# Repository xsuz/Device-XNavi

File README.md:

# Device-Template

> A template for building applications for Twelite

This project is developed and maintained by the xsuz

## Dependencies

To build embedded programs using this template you'll need:

- KiCad Version: 8.0.0, or a newer version.

- Git client

- Github CLI (optional)

## Using this template with GitHub CLI

```sh
gh repo create ${repo name} --private --template https://github.com/xsuz/Device-Template -c
cd ${repo name}
sh ./setup.sh
```

注. 自分のアカウントにRepositoryが作られます。

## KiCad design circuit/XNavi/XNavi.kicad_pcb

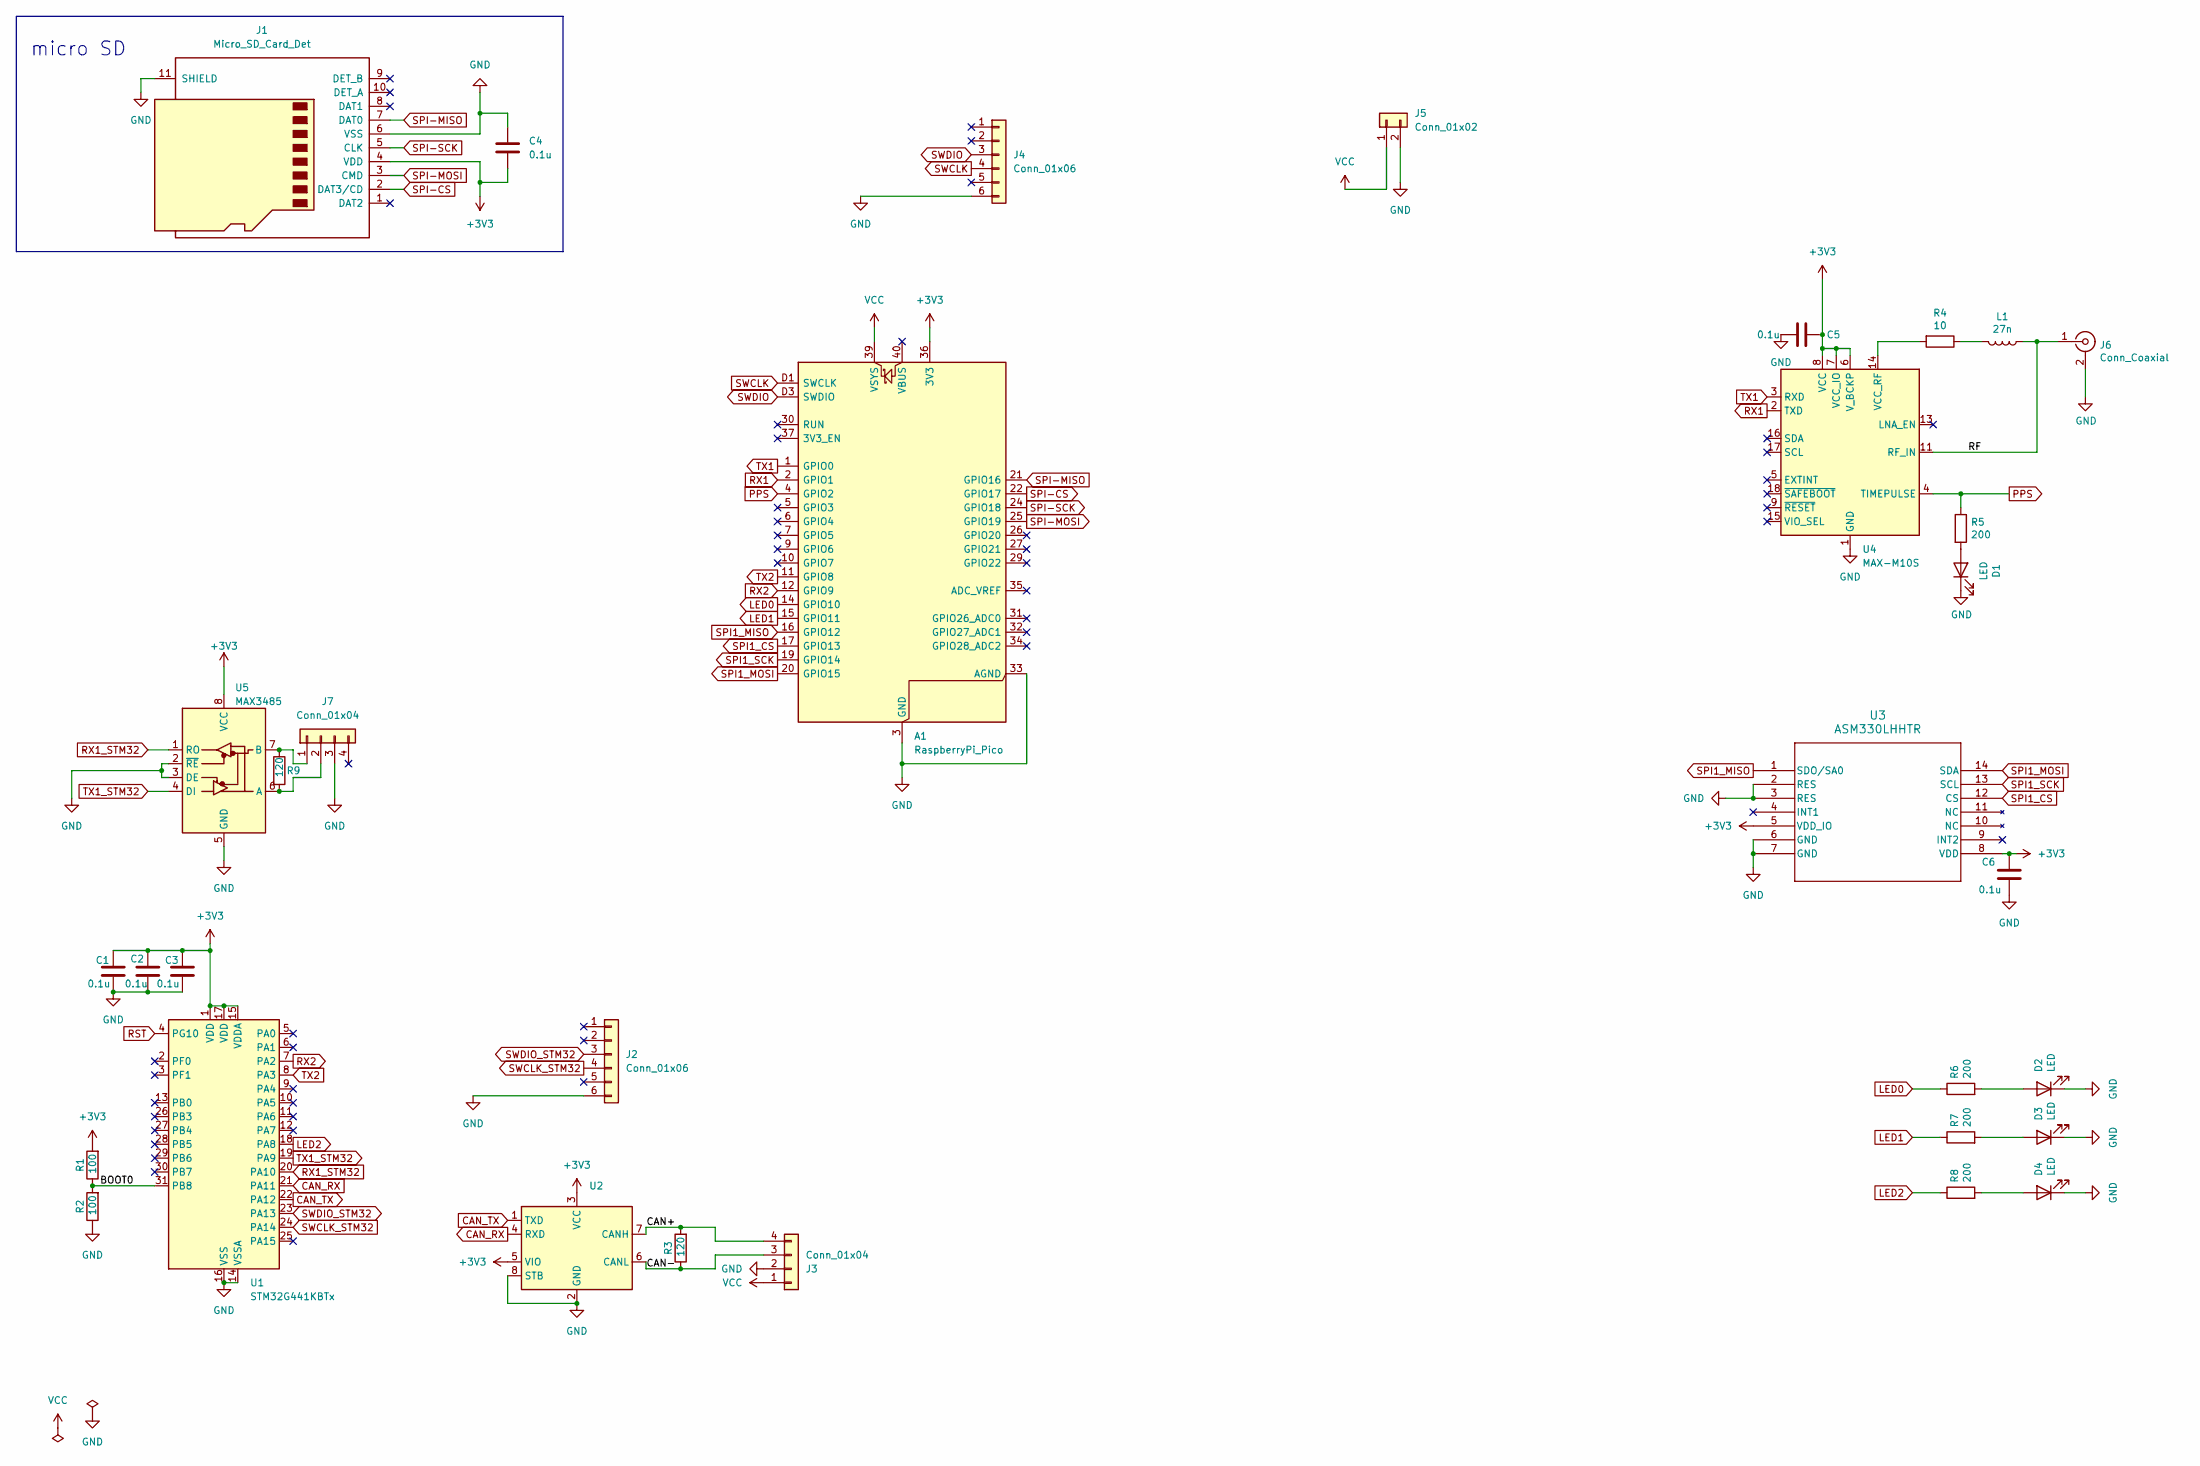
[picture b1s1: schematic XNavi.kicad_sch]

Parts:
A1: RaspberryPi_Pico; RaspberryPi_Pico_SMD_HandSolder
C1, C2, C3, C4, C5, C6: 0.1u; C_0603_1608Metric_Pad1.08x0.95mm_HandSolder
D1, D2, D3, D4: LED; D_0603_1608Metric_Pad1.05x0.95mm_HandSolder
J1: Micro_SD_Card_Det; microSD_HC_Hirose_DM3AT-SF-PEJM5
J2, J4: Conn_01x06; JST_ZH_B6B-ZR_1x06_P1.50mm_Vertical
J3, J7: Conn_01x04; JST_PH_S4B-PH-SM4-TB_1x04-1MP_P2.00mm_Horizontal
J5: Conn_01x02; JST_PH_S2B-PH-SM4-TB_1x02-1MP_P2.00mm_Horizontal
J6: Conn_Coaxial; U.FL_Molex_MCRF_73412-0110_Vertical
L1: 27n; L_0805_2012Metric_Pad1.15x1.40mm_HandSolder
R1, R2: 100; R_0603_1608Metric_Pad0.98x0.95mm_HandSolder
R3, R9: 120; R_0603_1608Metric_Pad0.98x0.95mm_HandSolder
R4: 10; R_0603_1608Metric_Pad0.98x0.95mm_HandSolder
R5, R6, R7, R8: 200; R_0603_1608Metric_Pad0.98x0.95mm_HandSolder
U1: STM32G441KBTx; LQFP-32_7x7mm_P0.8mm
U2: SOT-23-8_Handsoldering
U3: ASM330LHHTR; LGA-14_3x2.5mm_P0.5mm_LayoutBorder3x4y
U4: MAX-M10S; ublox_MAX
U5: MAX3485; SOP-8_3.76x4.96mm_P1.27mm

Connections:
+3V3: A1.36 (3V3), C1.1, C2.1, C3.1, C4.2, C5.1, C6.1, J1.4 (VDD), R1.2, U1.1 (VDD), U1.15 (VDDA), U1.17 (VDD), U2.3 (VCC), U2.5 (VIO), U3.5 (VDD_IO), U3.8 (VDD), U4.6 (V_BCKP), U4.7 (VCC_IO), U4.8 (VCC), U5.8 (VCC)
/BOOT0: R1.1, R2.2, U1.31 (PB8)
/CAN+: J3.4, R3.2, U2.7 (CANH)
/CAN-: J3.3, R3.1, U2.6 (CANL)
/RF: J6.1 (In), L1.1, U4.11 (RF_IN)
CAN_RX: U1.21 (PA11), U2.4 (RXD)
CAN_TX: U1.22 (PA12), U2.1 (TXD)
GND: A1.3 (GND), A1.8 (GND), A1.13 (GND), A1.18 (GND), A1.23 (GND), A1.28 (GND), A1.33 (AGND), A1.38 (GND), A1.D2 (GND), C1.2, C2.2, C3.2, C4.1, C5.2, C6.2, D1.1 (K), D2.1 (K), D3.1 (K), D4.1 (K), J1.6 (VSS), J1.11 (SHIELD), J2.6, J3.2, J4.6, J5.2, J6.2 (Ext), J7.3, R2.1, U1.14 (VSSA), U1.16 (VSS), U1.32 (VSS), U2.2 (GND), U2.8 (STB), U3.2 (RES), U3.3 (RES), U3.6 (GND), U3.7 (GND), U4.1 (GND), U4.10 (GND), U4.12 (GND), U5.2 (~RE), U5.3 (DE), U5.5 (GND)
LED0: A1.14 (GPIO10), R6.1
LED1: A1.15 (GPIO11), R7.1
LED2: R8.1, U1.18 (PA8)
unnamed: D1.2 (A), R5.2
unnamed: D2.2 (A), R6.2
unnamed: D3.2 (A), R7.2
unnamed: D4.2 (A), R8.2
unnamed: J7.1, R9.1, U5.7 (B)
unnamed: J7.2, R9.2, U5.6 (A)
unnamed: L1.2, R4.1
unnamed: R4.2, U4.14 (VCC_RF)
PPS: A1.4 (GPIO2), R5.1, U4.4 (TIMEPULSE)
RST: U1.4 (PG10)
RX1: A1.2 (GPIO1), U4.2 (TXD)
RX1_STM32: U1.20 (PA10), U5.1 (RO)
RX2: A1.12 (GPIO9), U1.7 (PA2)
SPI1_CS: A1.17 (GPIO13), U3.12 (CS)
SPI1_MISO: A1.16 (GPIO12), U3.1 (SDO/SA0)
SPI1_MOSI: A1.20 (GPIO15), U3.14 (SDA)
SPI1_SCK: A1.19 (GPIO14), U3.13 (SCL)
SPI-CS: A1.22 (GPIO17), J1.2 (DAT3/CD)
SPI-MISO: A1.21 (GPIO16), J1.7 (DAT0)
SPI-MOSI: A1.25 (GPIO19), J1.3 (CMD)
SPI-SCK: A1.24 (GPIO18), J1.5 (CLK)
SWCLK: A1.D1 (SWCLK), J4.4
SWCLK_STM32: J2.4, U1.24 (PA14)
SWDIO: A1.D3 (SWDIO), J4.3
SWDIO_STM32: J2.3, U1.23 (PA13)
TX1: A1.1 (GPIO0), U4.3 (RXD)
TX1_STM32: U1.19 (PA9), U5.4 (DI)
TX2: A1.11 (GPIO8), U1.8 (PA3)
VCC: A1.39 (VSYS), J3.1, J5.1

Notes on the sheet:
micro SD

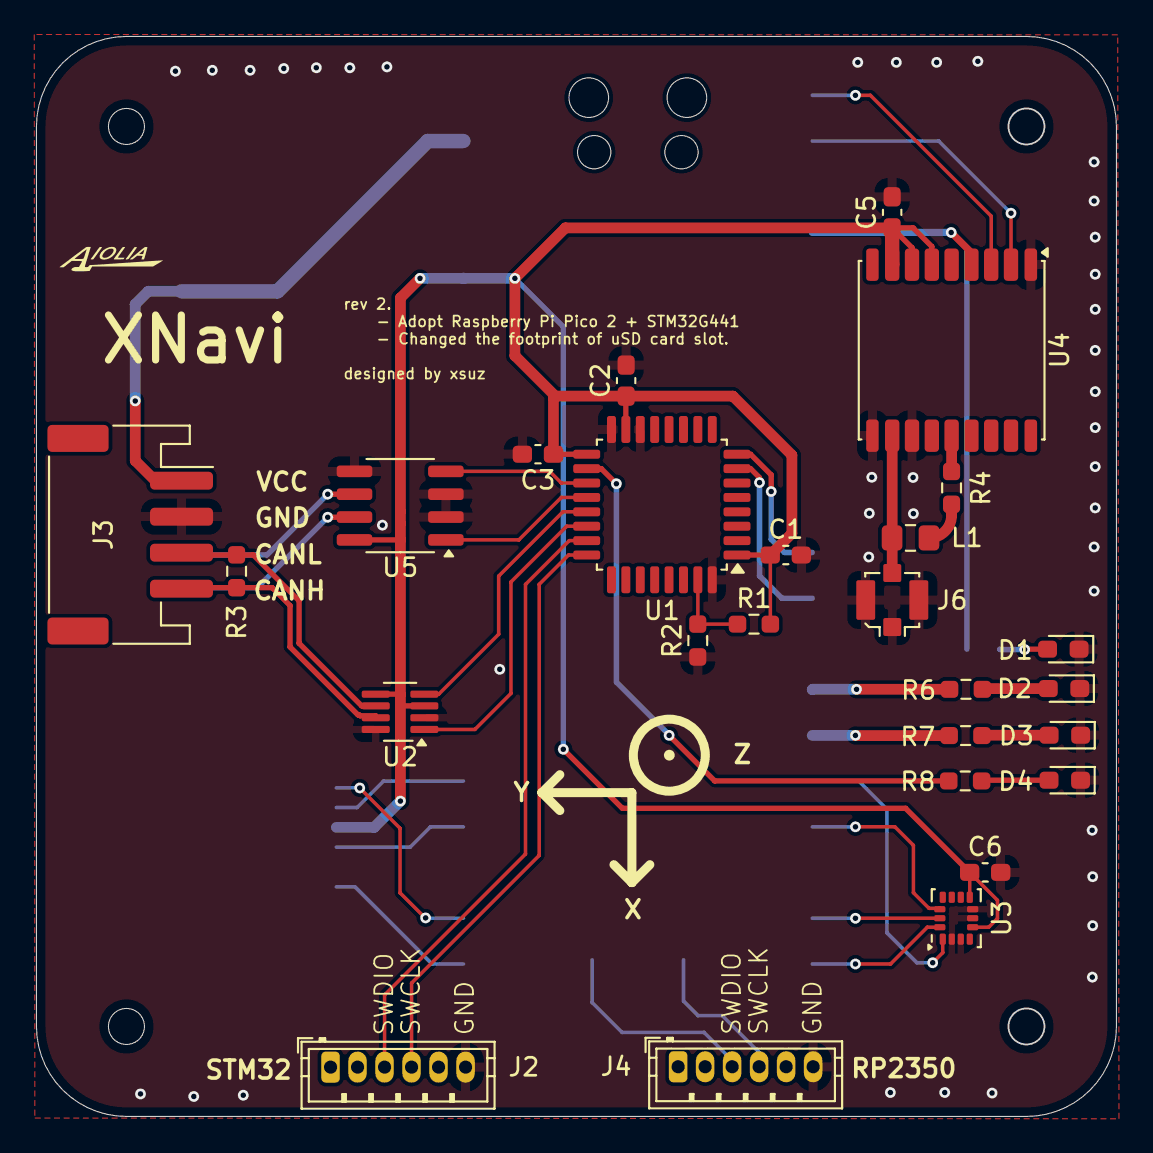
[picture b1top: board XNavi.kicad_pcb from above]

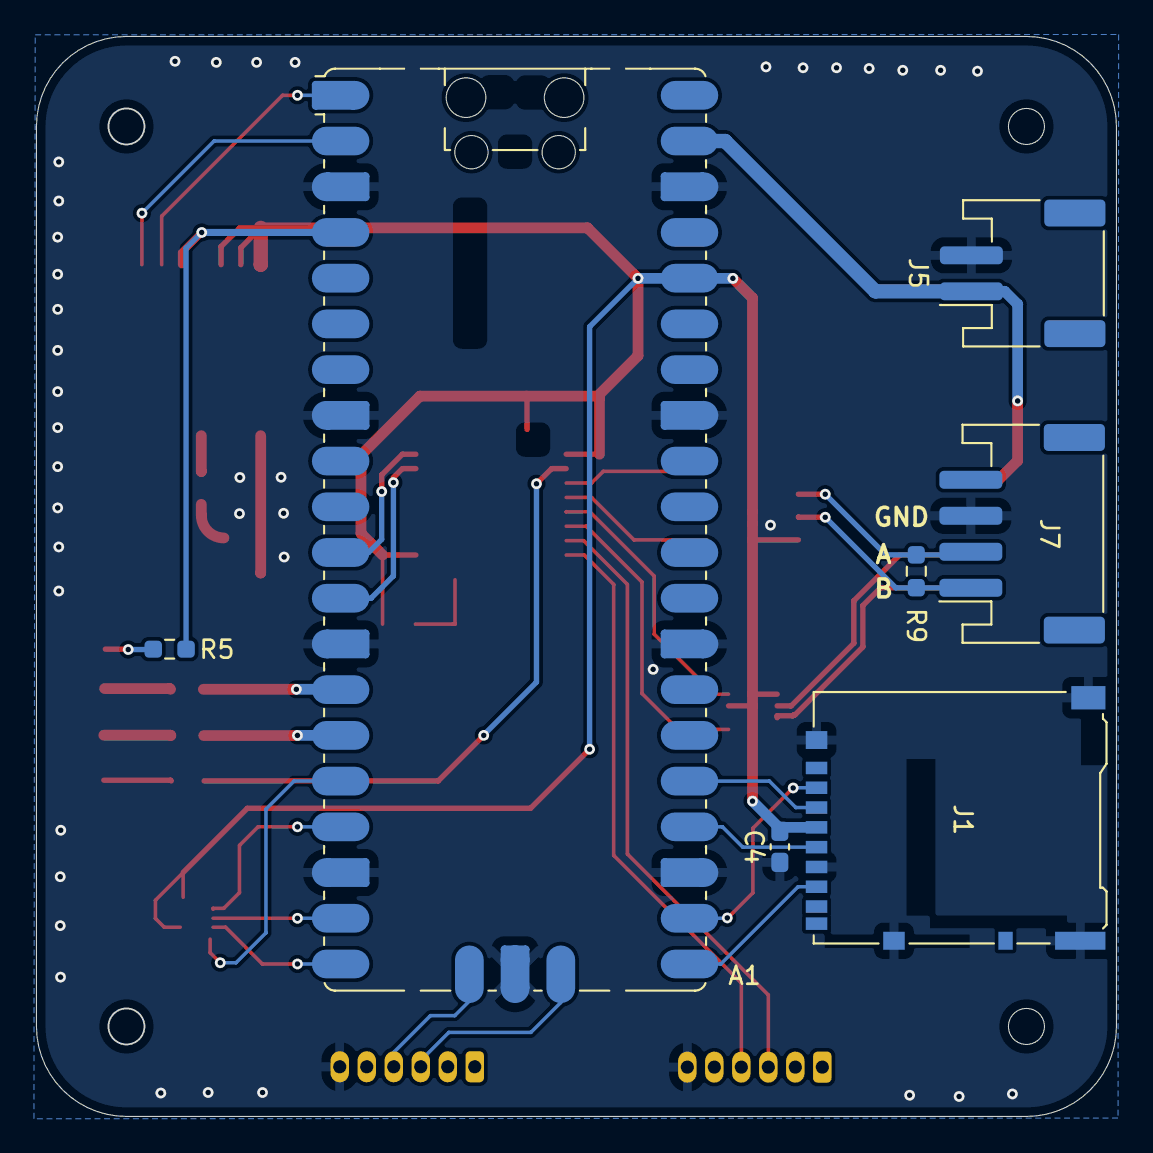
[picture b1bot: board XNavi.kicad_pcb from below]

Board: 2 copper layers, 60.0 x 60.0 mm, 33 parts (7 on the bottom side), 39 nets.

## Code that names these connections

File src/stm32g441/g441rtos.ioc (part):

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Mcu.Name=STM32G441KBTx
Mcu.Package=LQFP32
Mcu.UserName=STM32G441KBTx
PA11.Mode=FDCAN_Activate
PA11.Signal=FDCAN1_RX
PA12.Mode=FDCAN_Activate
PA12.Signal=FDCAN1_TX
PA13.Mode=Serial_Wire
PA13.Signal=SYS_JTMS-SWDIO
PA14.Mode=Serial_Wire
PA14.Signal=SYS_JTCK-SWCLK
PA2.Mode=Asynchronous
PA2.Signal=USART2_TX
PA3.Mode=Asynchronous
PA3.Signal=USART2_RX
PA8.GPIOParameters=GPIO_Label
PA8.GPIO_Label=LED
PA8.Signal=GPIO_Output
RCC.HSE_VALUE=8000000
RCC.SYSCLKFreq_VALUE=64000000
RCC.SYSCLKSource=RCC_SYSCLKSOURCE_PLLCLK
board=custom

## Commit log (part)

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2025-01-09 回路図&PCBを追加
2025-04-25 TCR3UF33Aを追加
2025-05-22 MCUをRaspberry Pi Pico(2)に変更
2025-05-29 RS485追加 & シルク追加
2025-06-10 UARTの信号線変更,基板を発注
2025-07-13 rp2350のプログラムを追加
2025-07-18 stm32g441のプログラムを追加
2025-07-18 SEGGER_RTTでログを吐き出す
2025-07-19 Queueを介してIMUDataを渡すようにした
2025-07-27 時刻補正の処理をsd_loggerから分離
2025-07-27 CAN busから受信したデータをrp2350に転送する処理を追加
2025-08-05 GPSによる時刻補正が完了するまで待機するようにした
2025-08-05 gnss関連の処理で使っていない変数を消した
2025-08-05 BOOTSELを押している間はログの保存を停止するようにした
2025-08-05 各タスクの優先度を変更
2025-08-06 readmeの内容を変更
2025-08-10 README追加
2025-08-10 Raspberry Pi Pico2内蔵のADCでVCCの電圧を取得するようにした．
2025-08-11 LEDの仕様を変更
2025-08-11 ubxのエラーハンドリングの改良 電池残量を推定
2025-08-12 cppに対応
2025-08-12 名前空間で囲った
2025-08-12 RP2350-STM32G441間で双方向に通信できるようにした
2025-08-12 FDCANを使うことにした
2025-08-12 STM32側にCOBSの処理をする時間を与えた
2025-08-12 stm32の起動を遅らせてcobsが正常に動くようにした
2025-08-13 XNavi内部とCAN busではLittle Endianで統一することに決定
2025-08-13 FDCANで送信できるようにする cobsのoverflowに対応
2025-08-15 FDCANで12byte以上のサイズのデータを受信できない問題を解決
2025-08-20 clockとFDCANの設定を変更
2025-08-21 RP2350が再起動するとUARTの通信が停止する問題を解決
2025-08-21 RTTのメッセージのフォーマットを定めた
2025-08-24 UARTの送信をDMAを介して行うようにした
2025-08-27 STM32側のbuild systemをCubeMX+CMakeの構成に変更
2025-08-28 vscodeのcmakeとdebug関連の設定を追加
2025-09-01 fatfsを更新
2025-09-01 README修正
2026-01-04 platformの指定方法を変更
2026-01-18 vscodeからrttの出力を見れるようにした
